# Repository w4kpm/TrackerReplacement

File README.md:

# Tracker replacement #

Directory Descriptions:
   * ChibiOS - A linked repo for the embedded OS
   * Firmware - Firmware code for the back panel
   * FrontPanelFirmware - Firmware code for the front panel
   * KiCad - all board design files using OSS KiCad
   * Testing - python files used for original testing of the board
   * TrackerControlCode - code use in production for updating tracker position and for resetting errors remotely. 

Included in this repo:
   * Board design files for user interface panel and tracker controller
   * Firmware for both interface panel and tracker controller
   * Examples of software used to control, reset and poll the tracker.
   * In KiCad/TrackerBackPanel and KiCad/TrackerFrontPanel are directories for gerber for board production
   * in KiCad/TrackerBackPanel/BackPanel.csv and KiCad/TrackerFrontPanel/FrontPanel.csv are parts lists
   * pos files are also there for SMT parts
   * back panel used polou VNH5019 motor driver board Item #1451 to control the motor

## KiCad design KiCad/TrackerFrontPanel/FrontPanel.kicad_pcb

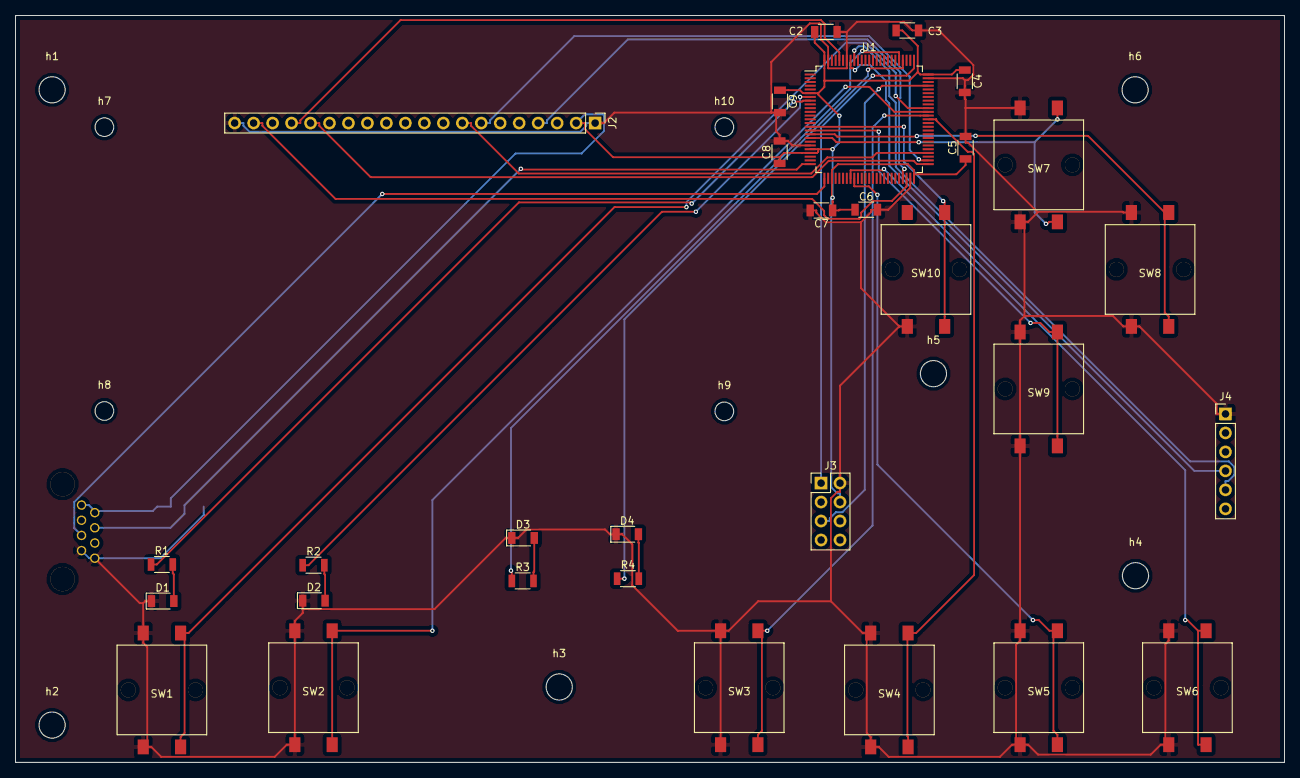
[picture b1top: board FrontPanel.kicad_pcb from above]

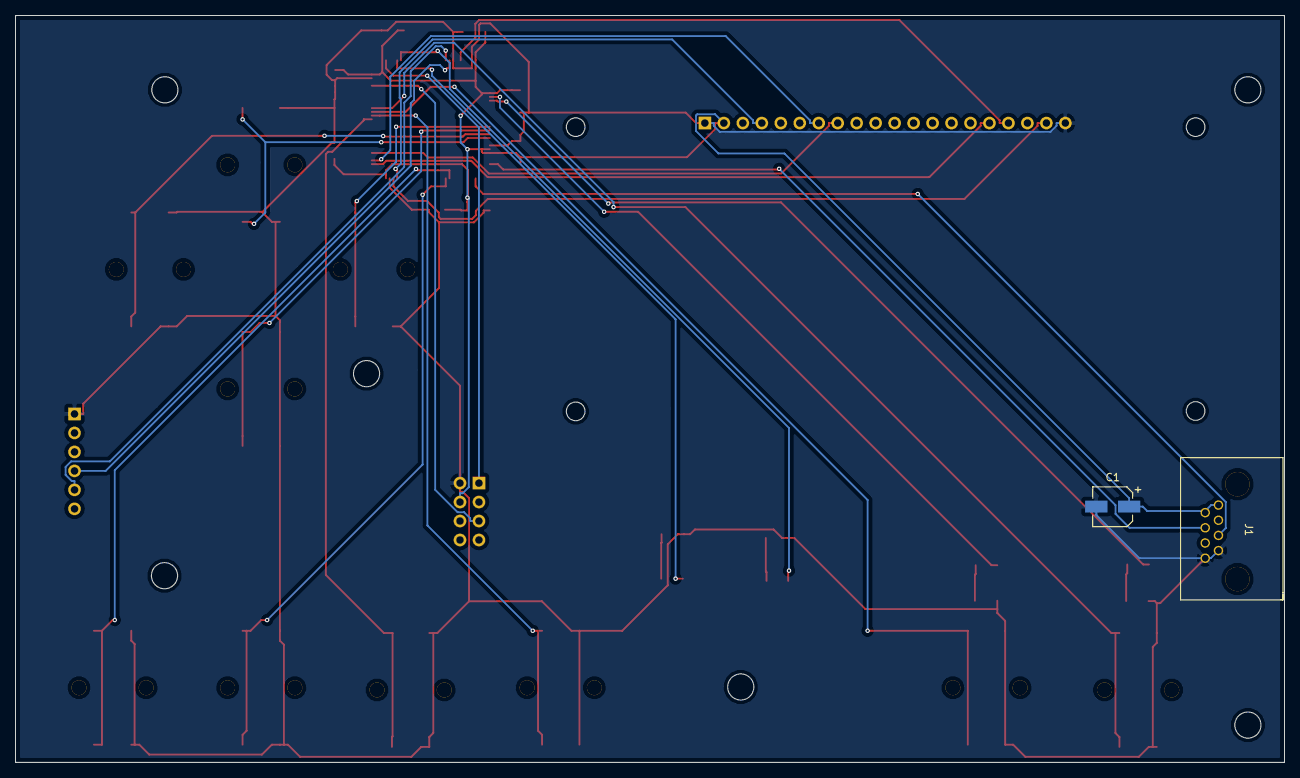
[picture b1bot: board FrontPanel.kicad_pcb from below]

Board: 2 copper layers, 169.9 x 100.0 mm, 42 parts (2 on the bottom side), 32 nets.

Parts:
C1: 100uF; CP_Elec_5x5.3
C2, C4, C6, C8: 1uF; C_1206
C3, C5, C7, C9: .1uF; C_1206
D1, D2, D3, D4: LED; D_1206
J1: Conn_01x08; RJ45
J2: Conn_01x20; Pin_Header_Straight_1x20_Pitch2.54mm
J3: Conn_02x04_Odd_Even; Pin_Header_Straight_2x04_Pitch2.54mm
J4: Conn_01x06; Pin_Header_Straight_1x06_Pitch2.54mm
R1, R2, R3, R4: R; R_1206
SW1, SW2, SW3, SW4, SW5, SW6, SW7, SW8, SW9, SW10: TS001; PTS125
U1: STM32F303V(B-C)Tx_u; LQFP-100_14x14mm_Pitch0.5mm
h1, h2, h3, h4, h5, h6: MountingHole_3.5mm
h7, h8, h9, h10: MountingHole_2.5mm

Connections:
+3V3: C1.1, C2.1, C3.1, C4.1, C5.1, C6.1, C7.1, C8.1, C9.1, J1.1, J1.2, J2.2, J3.4, U1.6, U1.21, U1.22, U1.28, U1.50, U1.75, U1.100
/RX: J1.5, U1.26
/TX: J1.4, U1.25
GND: C1.2, C2.2, C3.2, C4.2, C5.2, C6.2, C7.2, C8.2, C9.2, D1.1, D2.1, D3.1, D4.1, J1.7, J1.8, J2.1, J2.20, J3.2, J4.1, SW1.3, SW1.4, SW2.3, SW2.4, SW3.3, SW3.4, SW4.3, SW4.4, SW5.3, SW5.4, SW6.3, SW6.4, SW7.3, SW7.4, SW8.3, SW8.4, SW9.3, SW9.4, SW10.4, U1.20, U1.49, U1.74, U1.94, U1.99
unnamed: D1.2, R1.2
unnamed: D2.2, R2.2
unnamed: D3.2, R3.2
unnamed: D4.2, R4.2
unnamed: J2.4, U1.47
unnamed: J2.7, U1.52
unnamed: J2.8, U1.54
unnamed: J2.16, U1.51
unnamed: J2.17, U1.96
unnamed: J2.19, U1.48
unnamed: J3.1, U1.76
unnamed: J3.5, U1.72
unnamed: J4.4, U1.93
unnamed: J4.5, U1.92
unnamed: R1.1, U1.8
unnamed: R2.1, U1.7
unnamed: R3.1, U1.80
unnamed: R4.1, U1.79
unnamed: SW1.1, SW1.2, U1.66
unnamed: SW2.1, SW2.2, U1.65
unnamed: SW3.1, SW3.2, U1.64
unnamed: SW4.1, SW4.2, U1.63
unnamed: SW5.1, SW5.2, U1.34
unnamed: SW6.1, SW6.2, U1.33
unnamed: SW7.1, SW7.2, U1.18
unnamed: SW8.1, SW8.2, U1.17
unnamed: SW9.1, SW9.2, U1.16
unnamed: SW10.1, SW10.2, U1.15

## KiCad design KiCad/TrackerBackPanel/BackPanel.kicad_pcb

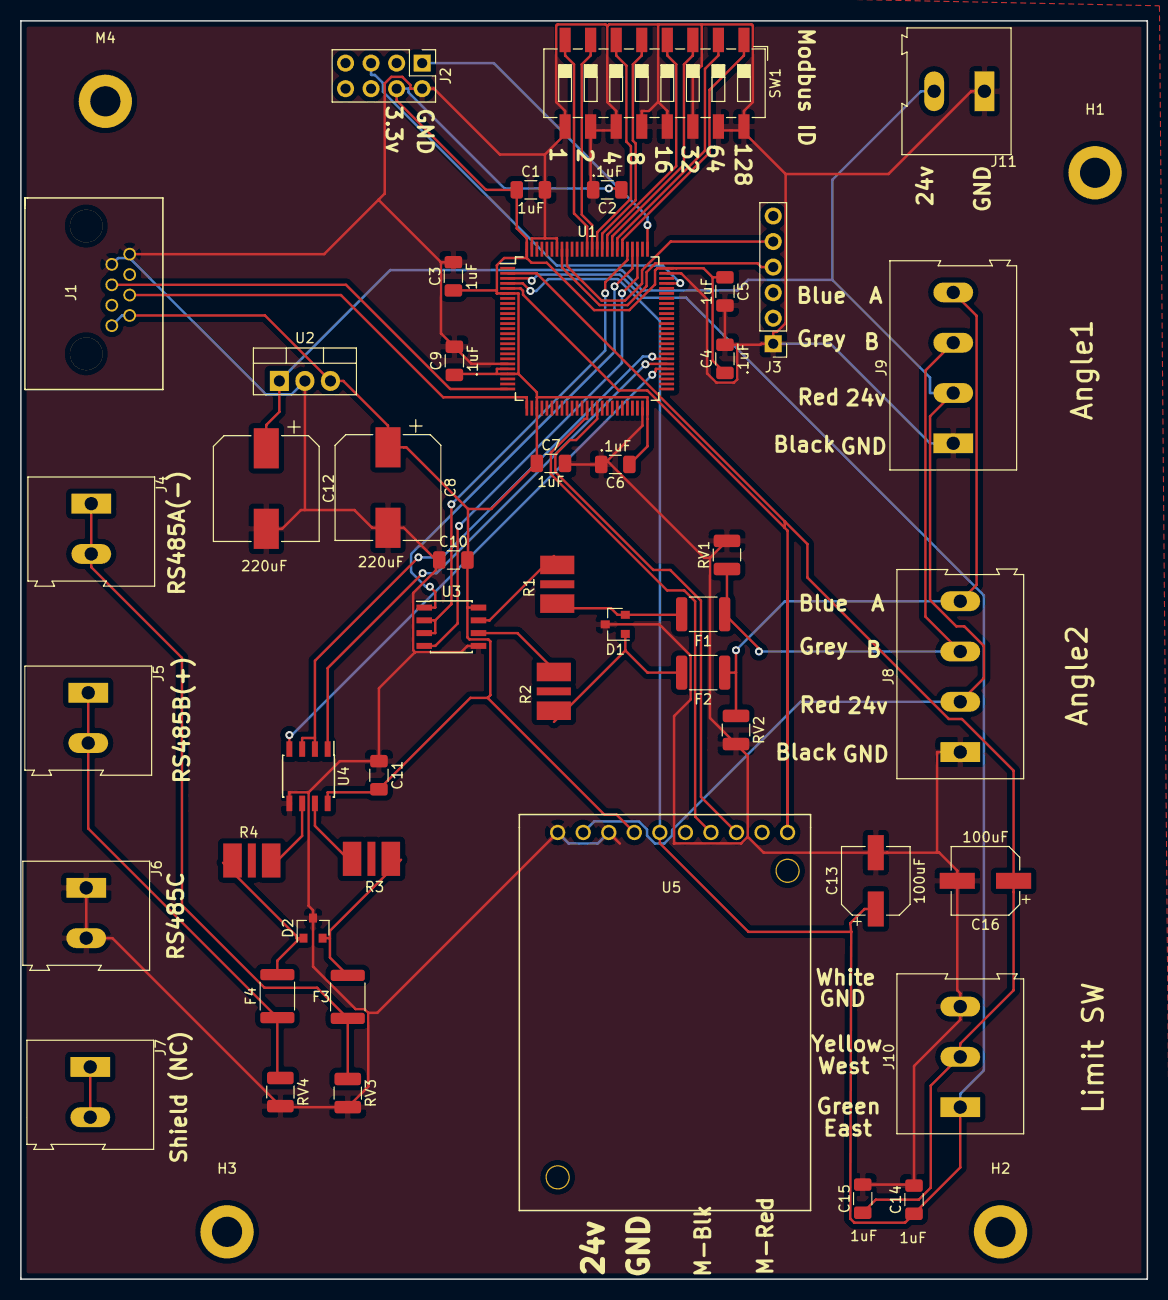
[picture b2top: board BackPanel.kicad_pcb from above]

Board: 2 copper layers, 112.0 x 125.1 mm, 51 parts (0 on the bottom side), 40 nets.

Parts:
C1, C3, C5, C7, C14, C15: 1uF; C_1206_3216Metric
C2, C4, C6, C9, C10, C11: .1uF; C_1206_3216Metric
C8, C12: 220uF; CP_Elec_10x10
C13, C16: 100uF; CP_Elec_6.3x5.2
D1, D2: D_TVS_x2_AAC; SOT-23
F1, F2, F3, F4: Polyfuse_Small; R_1812_4532Metric
H1, H2, H3: MountingHole_5.3mm_M5
J1: Conn_01x08; RJ45
J2: Conn_02x04_Odd_Even; PinHeader_2x04_P2.54mm_Vertical
J3: Conn_01x06; PinHeader_1x06_P2.54mm_Vertical
J4, J5, J6, J7, J11: Conn_01x02; TerminalBlock_Altech_AK300-2_P5.00mm
J8, J9: Conn_01x04; TerminalBlock_Altech_AK300-4_P5.00mm
J10: Conn_01x03; TerminalBlock_Altech_AK300-3_P5.00mm
M4: MountingHole_5.3mm_M5
R1, R2, R3, R4: TBU
RV1, RV2, RV3, RV4: Varistor; R_1210_3225Metric
SW1: SW-DIP-8; SW_DIP_SPSTx08_Slide_6.7x21.88mm_W8.61mm_P2.54mm_LowProfile
U1: STM32F303V(B-C)Tx_u; LQFP-100_14x14mm_P0.5mm
U2: R-78B3.3-2.0; TO-220-3_Vertical
U3, U4: SN65HV7X; SOIC-8_3.9x4.9mm_P1.27mm
U5: VNH5019; Pololu VNH5019 Breakout

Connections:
+3V3: C1.1, C2.1, C3.1, C4.1, C5.1, C6.1, C7.1, C8.1, C9.1, C10.2, C11.2, J1.1, J1.2, J2.4, U1.6, U1.21, U1.22, U1.28, U1.50, U1.75, U1.100, U2.3, U3.8, U4.8, U5.7
+24V: C12.1, J8.2, J9.2, J11.2, U2.1, U5.9
/C-D/RS485A(-): F3.1, J4.1, J4.2, RV3.1
/C-D/RS485B(+): F4.1, J5.1, J5.2, RV4.1
/C-D/serial/AngleRS485A(-): F2.1, J8.4, J9.4, RV2.1
/C-D/serial/AngleRS485B(+): F1.1, J8.3, J9.3, RV1.1
/C-D/serial/AngleRX: U1.79, U3.1
/C-D/serial/AngleTX: U1.78, U3.4
/C-D/serial/AngleTX_en: U1.80, U3.2, U3.3
/C-D/serial/RX: U1.56, U4.1
/C-D/serial/TX: U1.55, U4.4
/C-D/serial/TX_en: U1.57, U4.2, U4.3
/GPIOE/CurrentSense: U1.38, U5.4
/GPIOE/EastLimit: C13.1, C14.1, J10.1, U1.3, U1.4, U5.6
/GPIOE/GoWest: C15.1, C16.1, J10.2, U1.2, U1.5, U5.1
/GPIOE/pwm: U1.40, U5.3
/RX: J1.4, U1.26
/TX: J1.5, U1.25
GND: C1.2, C2.2, C3.2, C4.2, C5.2, C6.2, C7.2, C8.2, C9.2, C10.1, C11.1, C12.2, C13.2, C14.2, C15.2, C16.2, D1.3, D2.3, J1.7, J1.8, J2.2, J3.1, J6.1, J6.2, J8.1, J9.1, J10.3, J11.1, RV1.2, RV2.2, RV3.2, RV4.2, SW1.9, SW1.10, SW1.11, SW1.12, SW1.13, SW1.14, SW1.15, SW1.16, U1.20, U1.49, U1.74, U1.94, U1.99, U2.2, U3.5, U4.5, U5.8, U5.10
unnamed: D1.1, F2.2, R2.1
unnamed: D1.2, F1.2, R1.1
unnamed: D2.1, F4.2, R4.1
unnamed: D2.2, F3.2, R3.1
unnamed: J2.1, U1.76
unnamed: J2.5, U1.72
unnamed: J3.4, U1.93
unnamed: J3.5, U1.92
unnamed: J7.1, J7.2
unnamed: R1.2, U3.7
unnamed: R2.2, U3.6
unnamed: R3.2, U4.7
unnamed: R4.2, U4.6
unnamed: SW1.1, U1.81
unnamed: SW1.2, U1.82
unnamed: SW1.3, U1.83
unnamed: SW1.4, U1.84
unnamed: SW1.5, U1.85
unnamed: SW1.6, U1.86
unnamed: SW1.7, U1.87
unnamed: SW1.8, U1.88

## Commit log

2018-07-02 add example firmware from other location
2018-07-02 added submodule
2018-07-03 Added modbus comms for the angle sensor and added ADC for the amps out on the motor
2018-07-04 Update code for test at acorn - add set point, protections, etc)
2018-07-04 Added a modbus method to change the setpoint and limit switches in the main code
2018-09-10 added outline for front panel
2018-09-10 added new kicad project and supporting submodules
2018-09-10 add front panel schematic
2018-09-17 added old updates prior to installing kicad 5
2018-09-17 save prior to updating to kicad 5
2018-09-21 added back panel circuitboard
2018-10-02 get ready to transfer back to main computer
2018-10-02 update code to respond to commands from tty input & add test
2018-10-02 add code to timeout after an hour and then hide display - wake up on push of any button
2018-10-04 add code for new board
2018-10-15 add pwm for the motor
2018-10-15 Add pwm
2018-10-17 update circuit board with new changes;
2018-10-26 Transfer to new computer
2018-10-26 write parameters to flash
2018-10-26 I had the other in for temp - I need to add the updateid code
2018-10-29 Added ability to set parameters and save them to flash
2018-10-29 added updates to setting the angle - dont set under certian conditions
2018-11-08 finish off modbus features
2018-11-08 invert switch by software because board was labeled wrong
2018-12-03 Made a queue for the angles to better keep track of motion
2018-12-04 Make it so that angles dont "count up"
2020-08-04 Add all files and check in prior to mothballing
2022-08-25 add notes to control software
2022-08-25 Add toplevel readme
2022-08-25 add some comments about different directories
2022-08-25 make readme more readable
2022-08-25 Update readability of error codes
2022-08-25 remove unneeded files
